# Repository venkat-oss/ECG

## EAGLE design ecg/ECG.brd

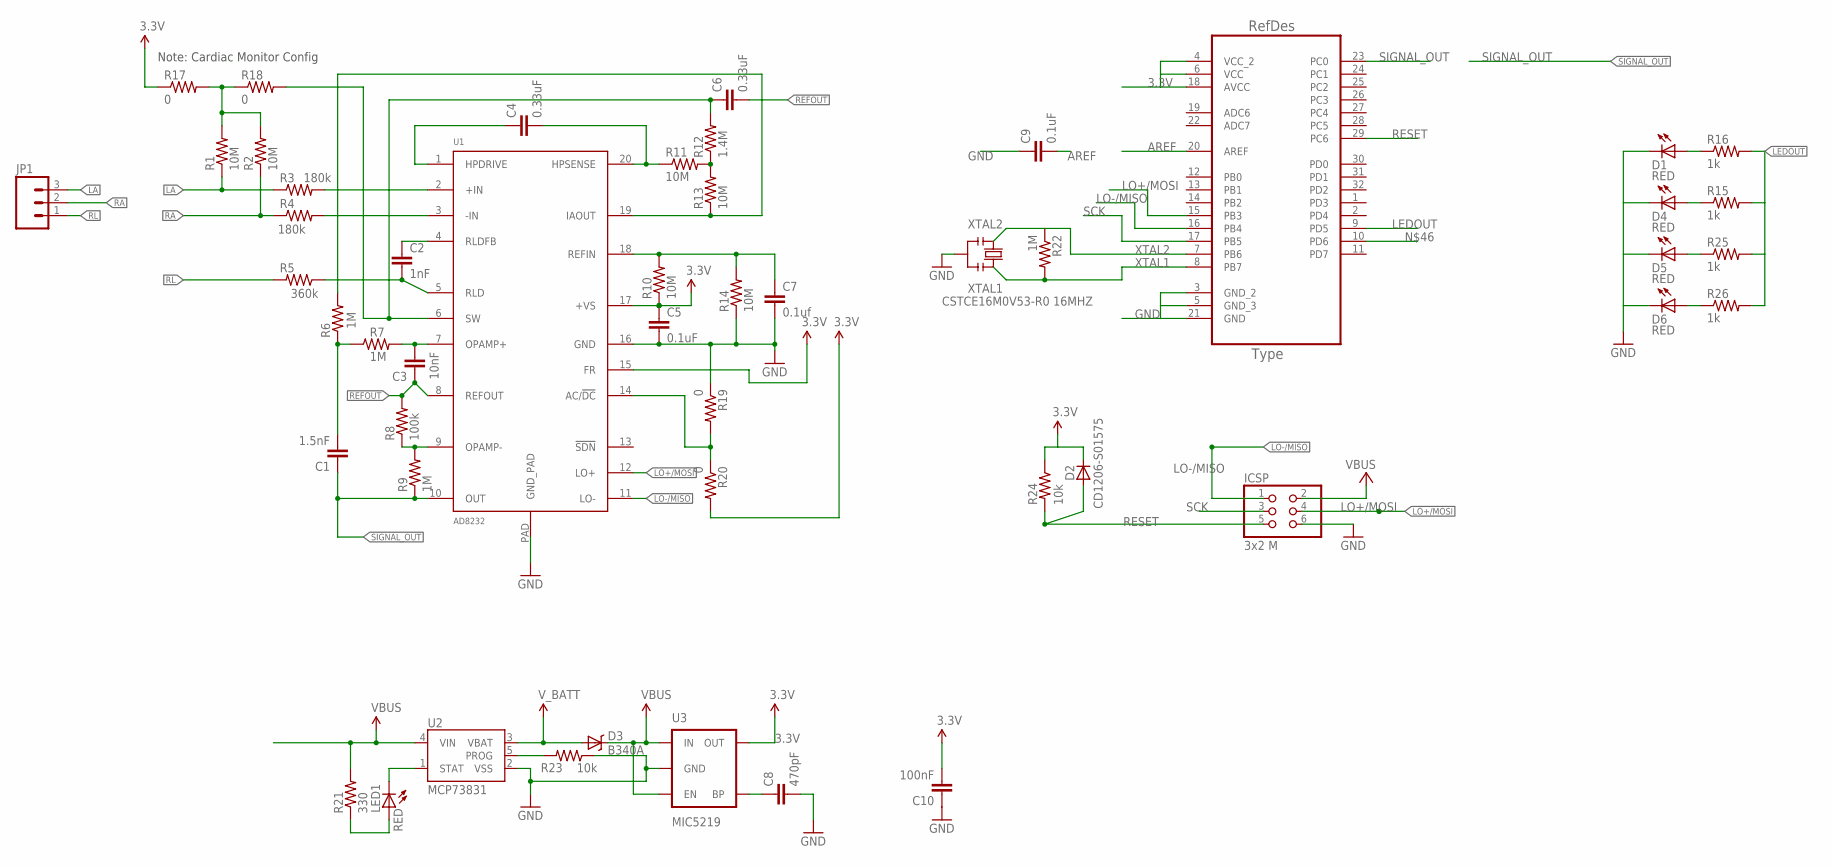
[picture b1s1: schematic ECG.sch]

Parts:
C1: 1.5nF; 0402-CAP
C2: 1nF; 0402-CAP
C3: 10nF; 0402-CAP
C4, C6: 0.33uF; 0805
C5, C9: 0.1uF; 0402-CAP
C7: 0.1uf; 0402-CAP
C8: 470pF; 0603-CAP
C10: 100nF; 0402-CAP
D1, D4, D5, D6: RED; LED-0603@1
D2: CD1206-S01575; MINIMELF
D3: B340A; SMA-DIODE
ICSP: 3x2 M; 2X03
JP1: M03PTH; 1X03
LED1: RED; LED-0603
R1, R2, R10, R11, R13, R14: 10M; 0402-RES
R3, R4: 180k; 0402-RES
R5: 360k; 0402-RES
R6, R7, R9, R22: 1M; 0402-RES
R8: 100k; 0402-RES
R12: 1.4M; 0402-RES
R15, R16, R25, R26: 1k; 0603-RES@1
R17, R18, R19, R20: 0; 0603
R21: 330; 0603-RES
R23: 10k; 0603-RES
R24: 10k; 0402-RES
U1: AD8232; LFCSP_20
U2: MCP73831; SOT23-5
U3: MIC5219; SOT23-5
U4: ATMEGA328P-AU; QFP80P900X900X120-32N
Y2: CSTCE16M0V53-R0 16MHZ; RESONATOR

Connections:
3.3V: C5.1, C10.2, D2.C, R10.1, R17.1, R20.2, R24.1, U1.15 (FR), U1.17 (+VS), U3.5 (OUT), U4.4 (VCC_2), U4.6 (VCC), U4.18 (AVCC)
AREF: C9.2, U4.20 (AREF)
GND: C5.2, C7.2, C8.2, C9.1, C10.1, D1.C, D4.C, D5.C, D6.C, ICSP.6, R14.1, R19.1, R23.1, U1.16 (GND), U1.PAD (GND_PAD), U2.2 (VSS), U3.2 (GND), U4.3 (GND_2), U4.5 (GND_3), U4.21 (GND), Y2.2
LA: JP1.3, R1.1, R3.1
LEDOUT: R15.2, R16.2, R25.2, R26.2, U4.9 (PD5)
LO+/MOSI: ICSP.4, U1.12 (LO+), U4.15 (PB3)
LO-/MISO: ICSP.1, U1.11 (LO-), U4.16 (PB4)
unnamed: R3.2, U1.2 (+IN)
unnamed: R4.2, U1.3 (-IN)
unnamed: C3.2, R7.2, U1.7 (OPAMP+)
unnamed: C4.2, R11.1, U1.20 (HPSENSE)
unnamed: C7.1, R10.2, R14.2, U1.18 (REFIN)
unnamed: D1.A, R16.1
unnamed: R8.1, R9.2, U1.9 (OPAMP-)
unnamed: R6.2, R13.1, U1.19 (IAOUT)
unnamed: C1.2, R6.1, R7.1
unnamed: R19.2, R20.1, U1.14 (AC/!DC)
unnamed: C4.1, U1.1 (HPDRIVE)
unnamed: R11.2, R12.1, R13.2
unnamed: LED1.A, R21.1
unnamed: C6.1, R12.2, R18.2, U1.6 (SW)
unnamed: C2.1, U1.4 (RLDFB)
unnamed: C2.2, R5.1, U1.5 (RLD)
unnamed: LED1.C, U2.1 (STAT)
unnamed: R1.2, R2.2, R17.2, R18.1
unnamed: R23.2, U2.5 (PROG)
unnamed: C8.1, U3.4 (BP)
unnamed: D6.A, R26.1
unnamed: D5.A, R25.1
unnamed: D4.A, R15.1
RA: JP1.2, R2.1, R4.1
REFOUT: C3.1, C6.2, R8.2, U1.8 (REFOUT)
RESET: D2.A, ICSP.5, R24.2, U4.29 (PC6)
RL: JP1.1, R5.2
SCK: ICSP.3, U4.17 (PB5)
SIGNAL_OUT: C1.1, R9.1, U1.10 (OUT), U4.23 (PC0)
VBUS: D3.C, ICSP.2, R21.2, U2.4 (VIN), U3.1 (IN), U3.3 (EN)
V_BATT: D3.A, U2.3 (VBAT)
XTAL1: R22.2, U4.8 (PB7), Y2.3
XTAL2: R22.1, U4.7 (PB6), Y2.1

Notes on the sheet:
Note: Cardiac Monitor Config

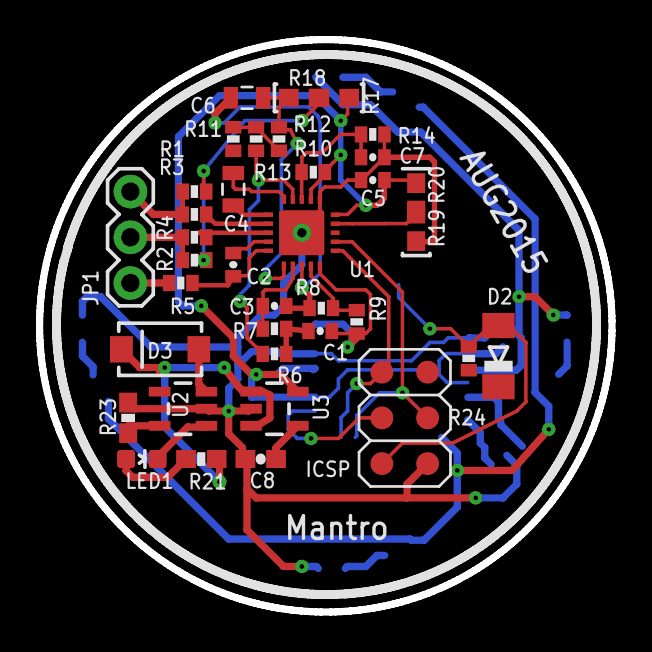
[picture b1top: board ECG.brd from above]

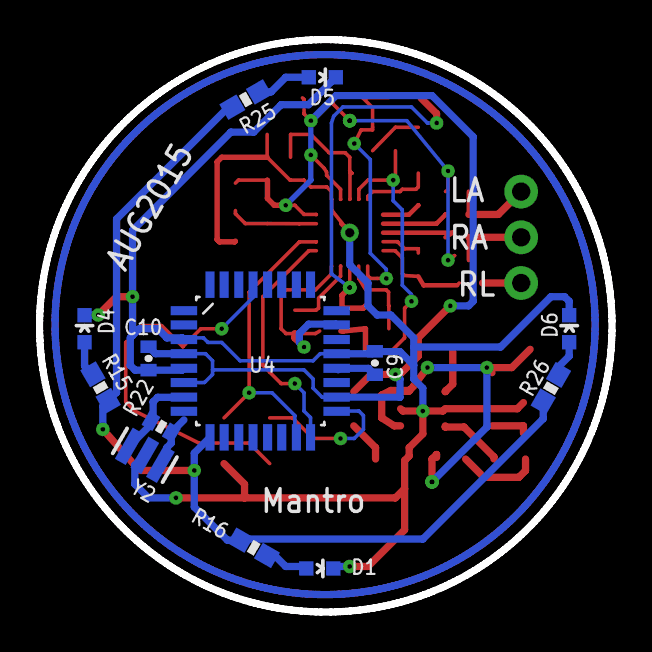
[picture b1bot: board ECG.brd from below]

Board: 2 copper layers, 31.8 x 31.8 mm, 51 parts (13 on the bottom side), 40 nets.

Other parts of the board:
DRILEGEND: DRILEGEND

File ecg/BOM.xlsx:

| Bill of materials for single board
Qty | Value | Device | Package | Parts | Description | Digi Key Part Number / Link
1 |  | M03PTH | 1X03 | JP1 | Header 3 | DO NOT STUFF
4 | 0 | 0OHM1/10W5%(0603) | 603 | R17, R18, R19, R20 | RES-08609 | RHM0.0GCT-ND
3 | 0.1uF | CAP0402-CAP | 0402-CAP | C5, C7, C9 | Capacitor | 490-6327-1-ND
2 | 0.33uF | CAP0805-CAP | 0805-CAP | C4, C6 | Capacitor | 490-3263-1-ND
1 | 1.4M | RESISTOR0402-RES | 0402-RES | R12 | Resistor | 541-1.40MLCT-ND
1 | 1.5nF | CAP0402-CAP | 0402-CAP | C1 | Capacitor | 399-8950-1-ND
1 | 100k | RESISTOR0402-RES | 0402-RES | R8 | Resistor | RHM100KCDCT-ND
1 | 100nF | CAP0402-CAP | 0402-CAP | C10 | Capacitor | 490-6327-1-ND
6 | 10M | RESISTOR0402-RES | 0402-RES | R1, R2, R10, R11, R13, R14 | Resistor | 311-10.0MLRCT-ND
1 | 10k | RESISTOR0402-RES | 0402-RES | R24 | Resistor | RHM10.0KCDCT-ND
1 | 10k | RESISTOR0603-RES | 0603-RES | R23 | Resistor | RHM10.0KHCT-ND
1 | 10nF | CAP0402-CAP | 0402-CAP | C3 | Capacitor | GRM155R71E103JA01J
2 | 180k | RESISTOR0402-RES | 0402-RES | R3, R4 | Resistor | RHM180KBHCT-ND
4 | 1M | RESISTOR0402-RES | 0402-RES | R6, R7, R9, R22 | Resistor | RHM1.00MCDCT-ND
4 | 1k | RESISTOR0603-RES | 0603-RES,1% | R15, R16, R25, R26 | 1k-ohm SMT | RHM1.00KCFCT-ND
1 | 1nF | CAP0402-CAP | 0402-CAP | C2 | Capacitor | 1276-1488-1-ND
1 | 330 | RESISTOR0603-RES | 0603-RES | R21 | Resistor | RHM330CFCT-ND
1 | 360k | RESISTOR0402-RES | 0402-RES | R5 | Resistor | RHM360KCDCT-ND
1 | 3x2 M | PINHD-2X3 | 2X03 | ICSP | PIN HEADER | DO NOT STUFF
1 | 470pF | CAP0603-CAP | 0603-CAP | C8 | Capacitor | PCF1449CT-ND
1 | AD8232 | AD8232 | LFCSP_20 | U1 | Analog Conditioner | AD8232ACPZ-R7CT-ND
1 | ATMEGA328P-AU | ATMEGA328P-AU | QFP80P900X900X120-32N | U4 | Microcontroller | ATMEGA328P-AURCT-ND
1 | B340A | DIODE-SCHOTTKY-B340A | SMA-DIODE | D3 | Schottky diode | B340A-FDICT-ND
1 | CD1206-S01575 | DIODE-MINIMELF | MINIMELF | D2 | Diode | CD1206-S01575CT-ND
1 | CSTCE16M0V53-R0 16MHZ | RESONATORMU | RESONATOR | Y2 | resonator | 490-1198-1-ND
1 | MCP73831 | MCP73831 | SOT23-5 | U2 | charge management controller | MCP73831T-2ATI/OTCT-ND
1 | MIC5219 | V_REG_MIC52193.3V | SOT23-5 | U3 | Voltage Regulator | 576-1281-1-ND
4 | RED | LED-RED0603 | LED-0603 | D1, D4, D5, D6 | Red LEDs | 160-1447-1-ND
1 | RED | LED-WHITE0603 | LED-0603 | LED1 | White LED | 160-1724-1-ND

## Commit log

2015-11-03 added files
    added design files and libraries

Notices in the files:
parts and their libraries:
SparkFun-Passives: Licensing: CC v3.0 Share-Alike You are welcome to use this library for commercial purposes.
SparkFun-DiscreteSemi: Licensing: Creative Commons ShareAlike 4.0 International - https://creativecommons.org/licenses/by-sa/4.0
